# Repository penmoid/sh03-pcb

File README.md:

# SH03 controller

SH03 controller is an ESP32-S3-DevKitC-1 carrier board for the Sovol SH03
filament dryer. The board is a two-layer, 100 × 56 mm design. It carries nine
back-side SMD references: J1, J2, R1-R4, and C1-C3. J3 and the DevKitC-1
headers are through-hole parts fitted by the builder.

This repository contains the KiCad source, custom footprints, schematic
exports, fabrication files, renders, validation reports, and regeneration
scripts. The current design is Rev-A.

## Validation status

The repository documents CAD, DRC/ERC, routing, placement, and fabrication
checks. The project author has personally validated correct operation of the
assembled Rev-A board in the dryer. Perform the checks in
[docs/bring-up.md](docs/bring-up.md) before connecting a board to a dryer.

No firmware is included. The GPIO assignments are documented in
[docs/gpio-remap.md](docs/gpio-remap.md).

## Fabrication

The upload package is in [fab/](fab/). Read [fab/README.md](fab/README.md)
before ordering. The package contains Gerbers, a BOM, a CPL, and a STEP
export.

The BOM and sourcing notes are in [docs/bom.md](docs/bom.md). Connector mate
compatibility and all order-time sourcing information require confirmation
before an order.

## Images

The angled render does not include a resolved J2 3D model.

## Toolchain

The source was generated and checked with KiCad 10.0.5. The scripts use the
standalone `pcbnew` Python module. The fab guide includes the `kicad-cli`
commands for Gerbers, drills, CPL, SVG, 3D renders, and schematic PDF export.

The board generation pipeline is documented in
[docs/layout-plan.md](docs/layout-plan.md):

```text
scripts/place_footprints.py
scripts/route_board.py
scripts/add_ground_pour.py
scripts/add_fiducials.py
```

Run `scripts/check_placement.py`, `scripts/report_pads.py`, and
`scripts/check_determinism.py` after regeneration.

## Licensing

Hardware and documentation are covered by [CERN-OHL-P-2.0](LICENSE).
Scripts are covered by [MIT](LICENSES/MIT.txt). See [NOTICE.md](NOTICE.md) for
third-party and KiCad-derived footprint exceptions.

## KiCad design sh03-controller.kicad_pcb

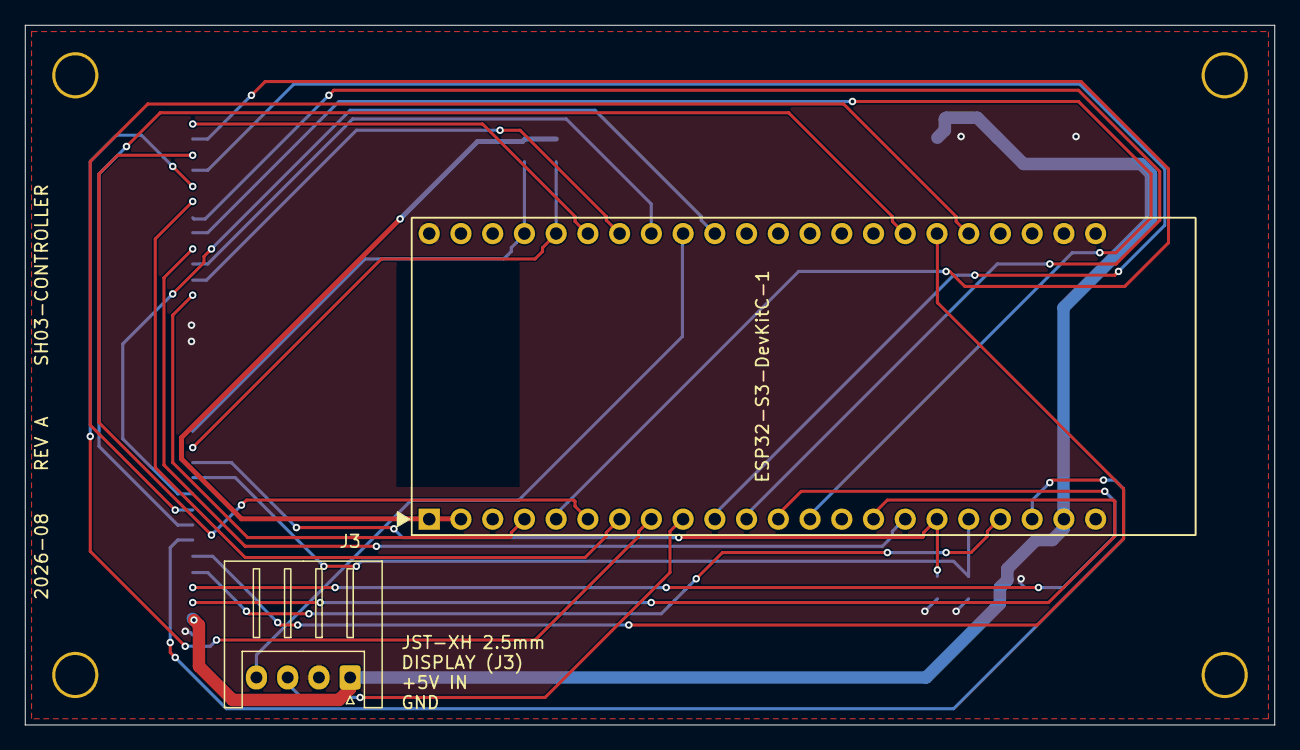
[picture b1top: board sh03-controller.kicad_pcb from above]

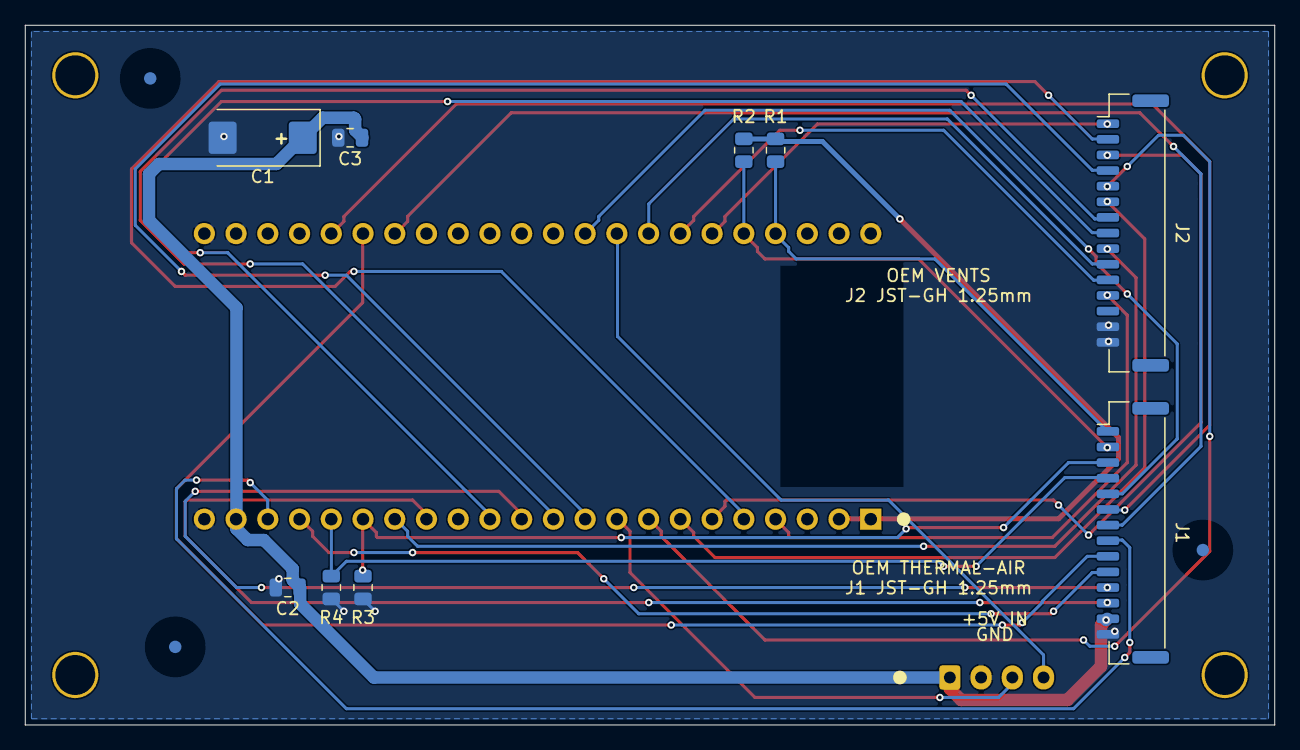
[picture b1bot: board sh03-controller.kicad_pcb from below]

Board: 2 copper layers, 100.0 x 56.0 mm, 18 parts (12 on the bottom side), 29 nets.

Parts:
C1: 470uF/10V polymer; CP_EIA-7343-43_Kemet-X_HandSolder
C2: 100nF; C_0805_2012Metric
C3: 10uF; C_0805_2012Metric
FID1, FID2, FID3: FIDUCIAL
H1, H2, H3, H4: MountingHole; MountingHole_3.2mm
J1: OEM_J1_thermal_air; JST_GH_BM14B_UNIVERSAL_1x14-1MP_P1.25mm_Vertical
J2: OEM_J2_vents; JST_GH_BM15B_UNIVERSAL_1x15-1MP_P1.25mm_Vertical
J3: AUX_display_umbilical; JST_XH_S4B-XH-A_1x04_P2.50mm_Horizontal
R1, R2: 33k; R_0805_2012Metric
R3, R4: 10k; R_0805_2012Metric
U1: ESP32-S3-DevKitC-1; ESP32-S3-DevKitC-1-Socket

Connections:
/+3V3: R1.1, R2.1, U1.1, U1.2
/+5V: C1.1, C2.1, C3.1, J1.13, J3.1, U1.21
/GND: C1.2, C2.2, C3.2, J1.14, J2.14, J2.15, J3.2, R3.2, R4.2, U1.22, U1.23, U1.43, U1.44
/MCU_RX: J3.4, U1.31
/MCU_TX: J3.3, U1.9
/MC_HALLA: J2.12, U1.4
/MC_HALLB: J2.9, U1.16
/MC_HALLC: J2.6, U1.7
/MC_HALLD: J2.3, U1.6
/MC_HOT1: J1.4, R4.1, U1.18
/MC_HOT2: J1.3, R3.1, U1.17
/MC_HUM_SCL: J1.12, U1.15
/MC_HUM_SDA: J1.11, U1.12
/MC_K_FAN1: J1.10, U1.19
/MC_K_FAN1_FG: J1.9, U1.39
/MC_K_FAN2: J1.8, U1.20
/MC_K_FAN2_FG: J1.7, U1.38
/MC_K_FAN3: J1.6, U1.40
/MC_K_FAN3_FG: J1.5, U1.32
/MC_XQA1: J2.11, U1.29
/MC_XQA2: J2.10, U1.30
/MC_XQB1: J2.8, U1.13
/MC_XQB2: J2.7, U1.11
/MC_XQC1: J2.5, U1.8
/MC_XQC2: J2.4, U1.10
/MC_XQD1: J2.2, U1.5
/MC_XQD2: J2.1, U1.28
/TH1: J1.2, R2.2, U1.27
/TH2: J1.1, R1.2, U1.26

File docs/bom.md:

# Bill of materials

This file records the parts used by the Rev-A board and the alternatives that
must be checked before an order. Values and part numbers are design data.
Distributor stock, pricing, and assembly-library status change over time.

## SMD parts

| Ref | Value | Part | LCSC | Library |
|---|---|---|---|---|
| C1 | 470 µF, 10 V, MnO2 tantalum, EIA 7343-43 | Kyocera AVX TPSE477K010R0100 | `C444831` | Extended |
| R1, R2 | 33k, 0805, 1% | Uniroyal Elec 0805W8F3302T5E | `C17633` | Basic |
| R3, R4 | 10k, 0805, 1% | Uniroyal Elec 0805W8F1002T5E | `C17414` | Basic |
| C2 | 100nF, 50V, X7R, 0805 | YAGEO CC0805KRX7R9BB104 | `C49678` | Basic |
| C3 | 10uF, 25V, X5R, 0805 | Samsung Electro-Mechanics CL21A106KAYNNNE | `C15850` | Basic |

C1 is the 5 V rail bulk capacitor. The design uses a 10 V rating and a 50%
voltage derating target. The estimated 1 ms, 300 mA transient produces about
640 mV of capacitive droop at 470 µF and about 30 mV of ESR step at 100 mΩ.
The earlier candidate was KEMET T530X477M010A*E020. It is not used in Rev-A.

All nine SMD references are on B.Cu for single-side assembly: J1, J2, R1-R4,
and C1-C3. C1 is polarized. Confirm its positive marking in the assembly
viewer and on the assembled board.

## Connectors and through-hole parts

| Ref | Part | Notes |
|---|---|---|
| J1 | BM14B-GHS-TBT, or GH125-S14CCA-00 (`C2886792`) | 14-position GH connector |
| J2 | BM15B-GHS-TBT, or GH125-S15CCA-00 (`C2886793`) | 15-position GH connector |
| J3 | JST XH 4-position right-angle | Through-hole, fitted by the builder |
| U1 | ESP32-S3-DevKitC-1 | Suitable 2×22, 2.54 mm headers/socket arrangement, or direct solder |

J1's genuine JST part is BM14B-GHS-TBT (`C265384`). J2's genuine JST part is
BM15B-GHS-TBT. The JUSHUO GH125 parts are JLCPCB Extended-library options.
The custom footprints cover the pad envelopes for the genuine and clone parts.
The clone-to-genuine-housing mate was unverified when the order package was
prepared. A genuine JST connector has a reported fit with the genuine JST
housings. That report does not prove clone compatibility. Test each clone and
housing combination before an assembly run.

The cable-side housings are GHR-14V-S (`C566400`) and GHR-15V-S (`C594572`).
The GH crimp contact is SSHL-002T-P0.2. The cut-tape part is
`MINI-SSHL-002T-P0.2`. `SXH-001T-P0.6` is an XH-series contact and is not a
GH substitute.

A 14- or 15-position cable requires a matching cable assembly, loose contacts
and a housing, or a re-terminated OEM cable. The pre-crimped GH-to-GH
AGHGH28K152 assembly is an option to evaluate. Confirm its pin-to-pin
continuity before use.

## Electrical constraints

R3 and R4 are mandatory 10k heater pull-downs. Do not power the dryer through
this board with either resistor missing.

J2 pin 13 is intentionally no-connect. The driver-board 3V3 signal is isolated
on this revision. Do not populate or wire it as a 3V3 output.

The connector choice, cable construction, housing mate, and order-time
assembly-library availability remain order checks. This document does not
claim that any distributor inventory is current.
